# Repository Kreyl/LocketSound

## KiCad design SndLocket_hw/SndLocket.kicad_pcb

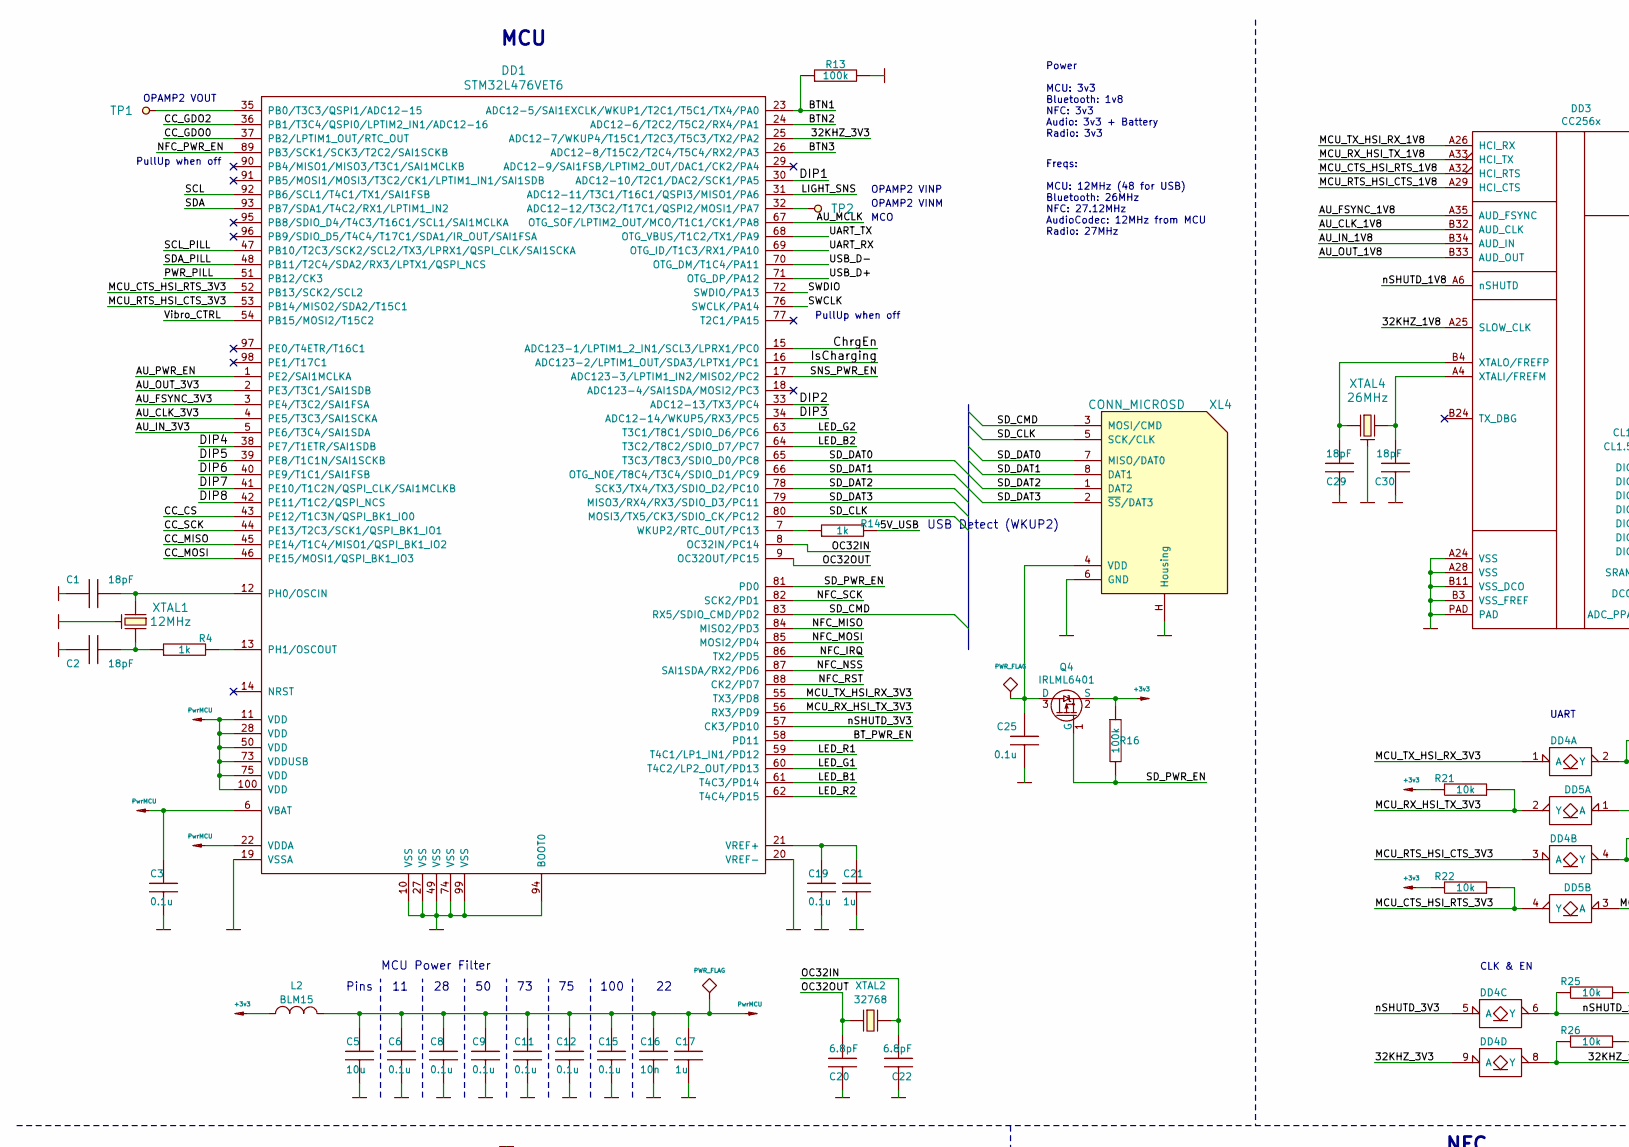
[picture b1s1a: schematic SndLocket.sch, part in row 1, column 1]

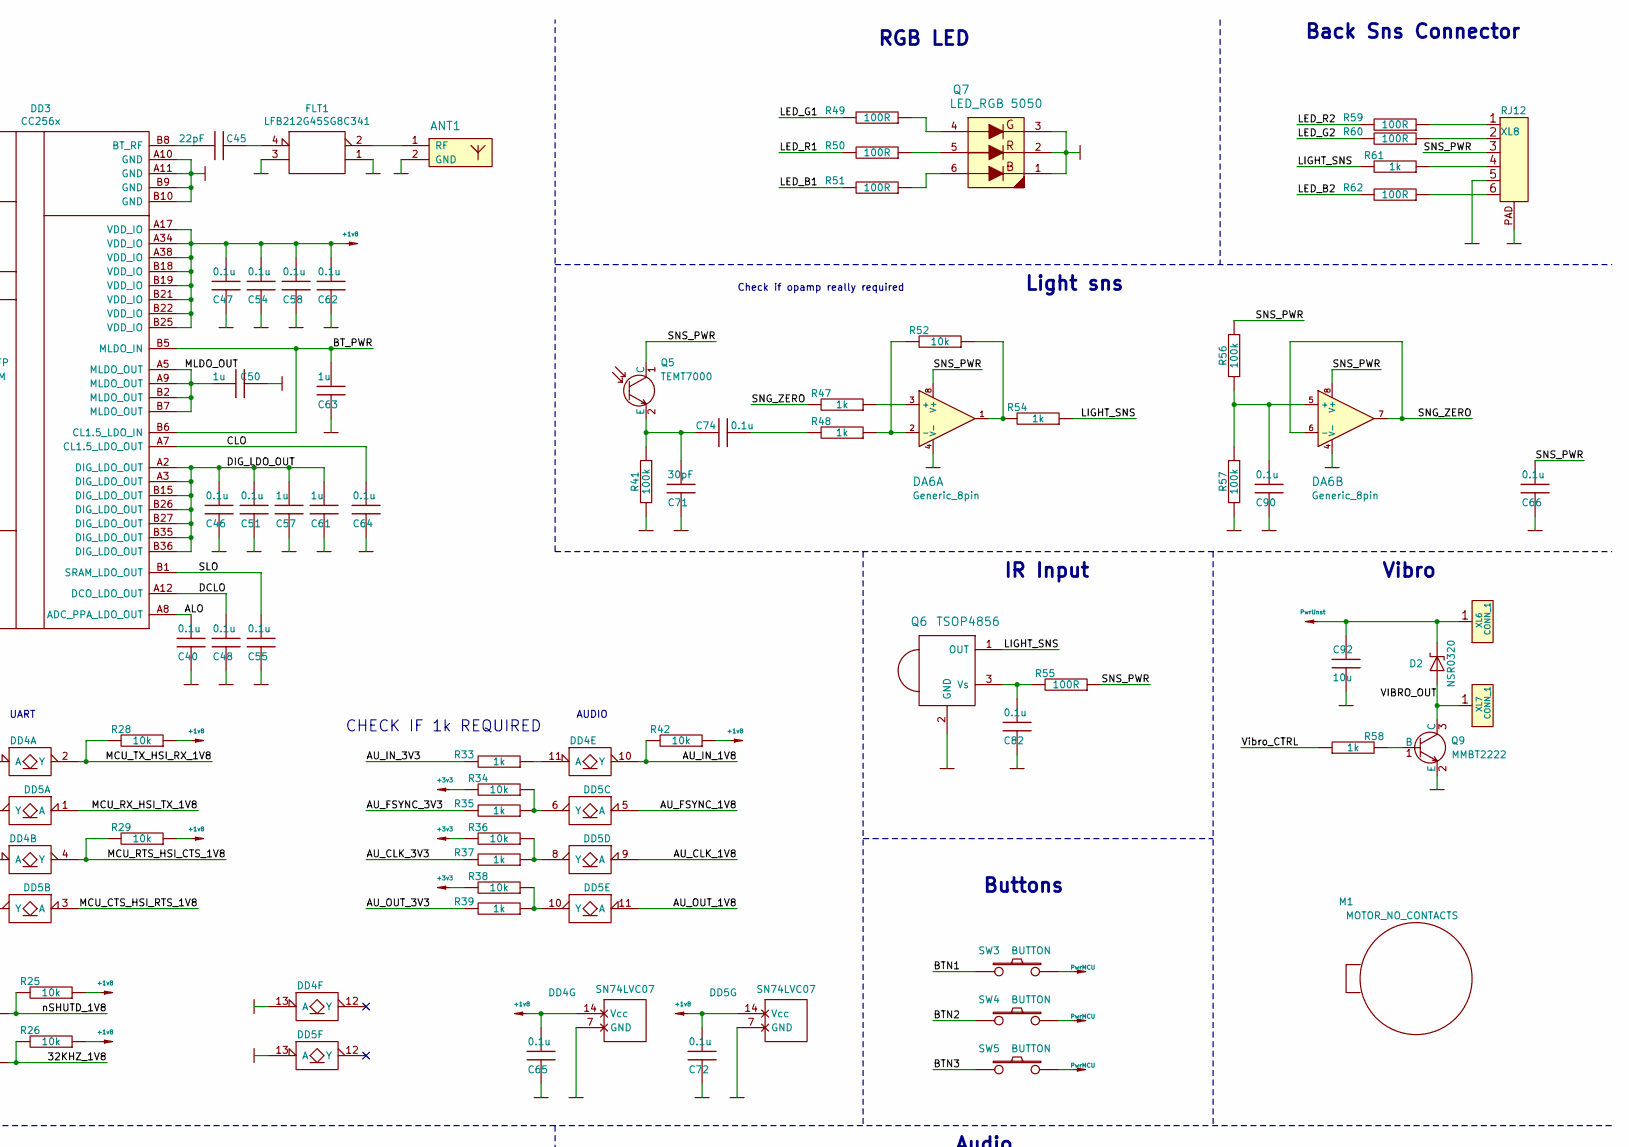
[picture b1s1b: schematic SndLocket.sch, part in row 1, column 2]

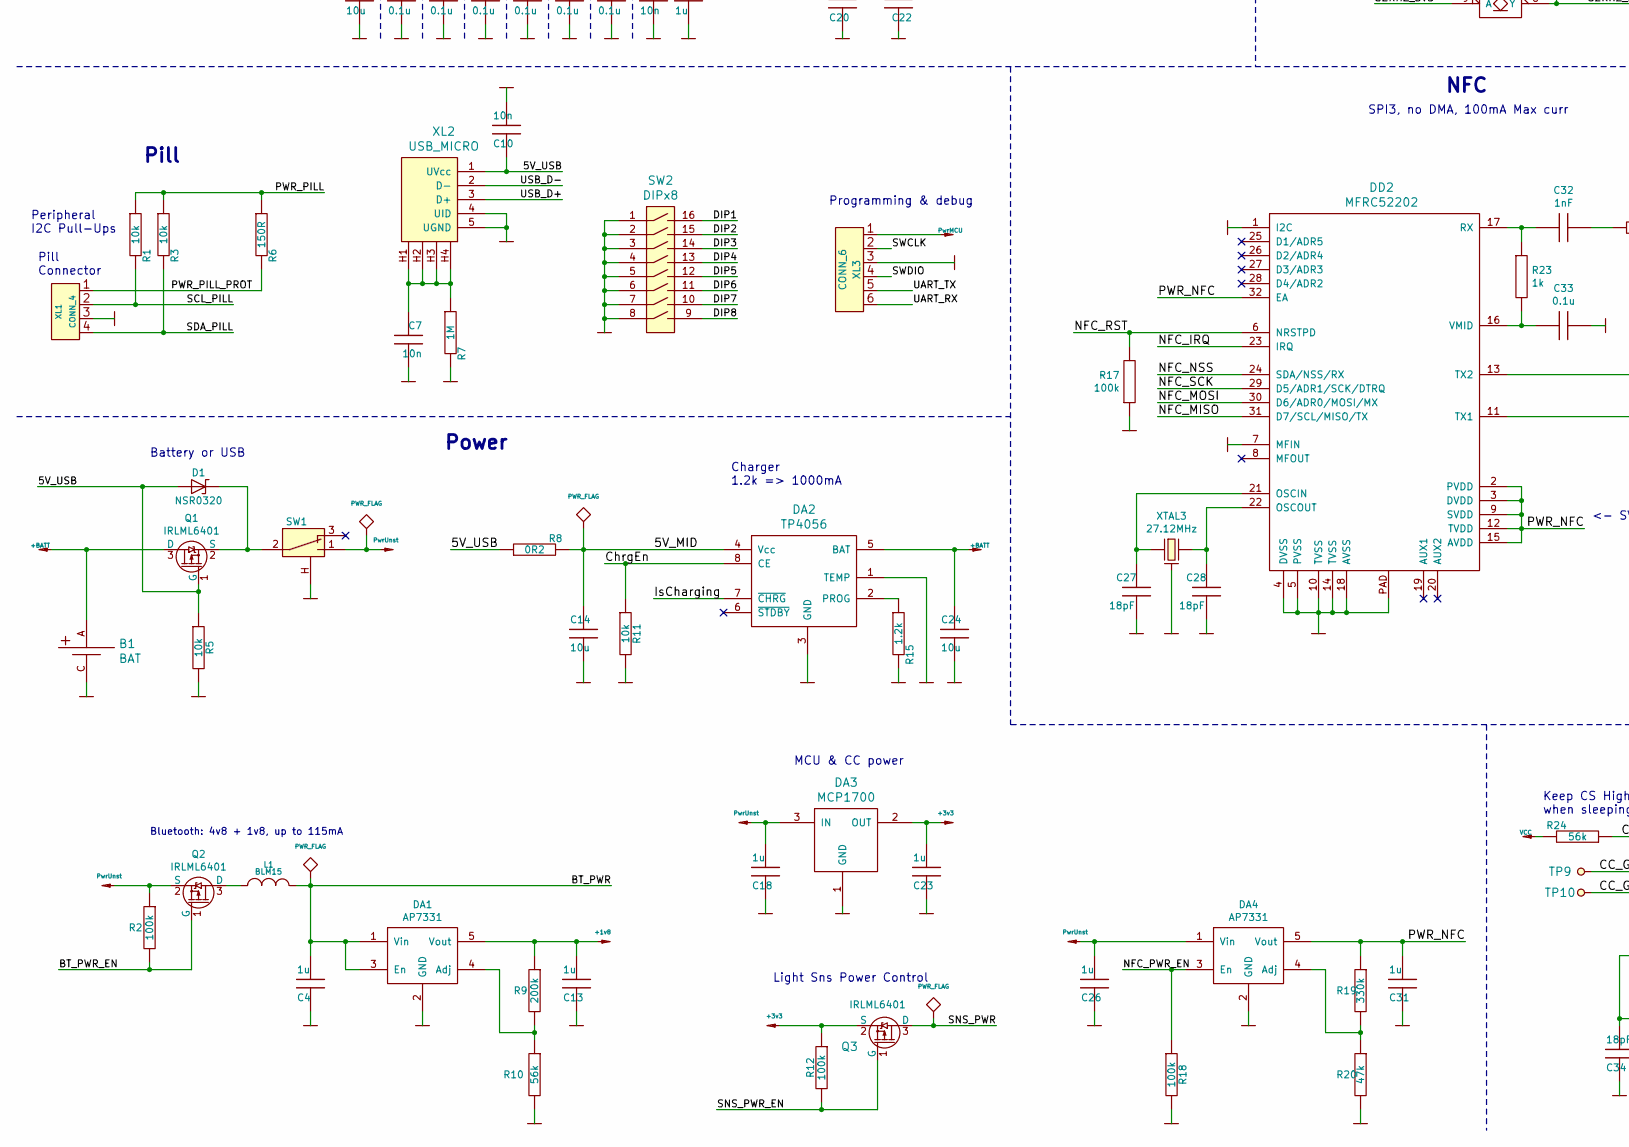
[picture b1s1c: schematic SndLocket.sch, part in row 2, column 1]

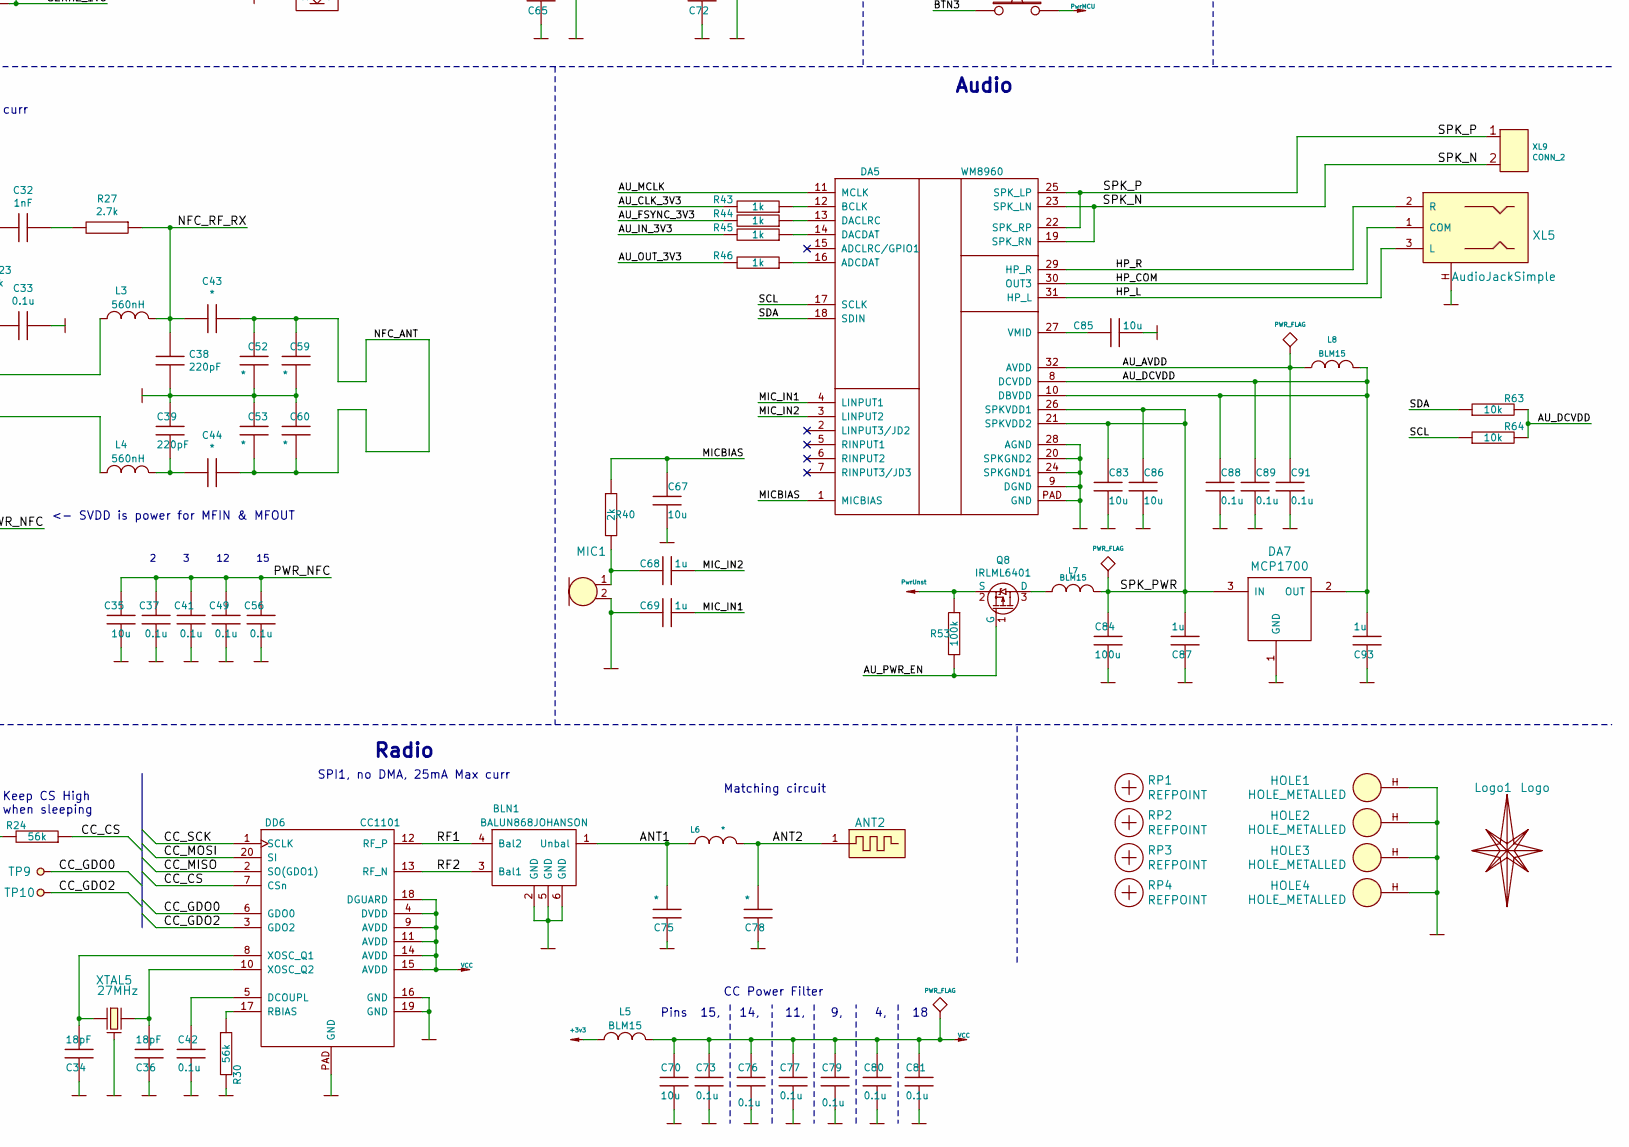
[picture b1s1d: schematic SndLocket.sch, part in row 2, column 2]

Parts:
ANT1: ANT_GENERAL; LcktSnd_2d41
ANT2: ANT_PCB_MONO_2PIN; LcktSnd_868
B1: BAT; 18650x1
BLN1: BALUN868JOHANSON; BALUN_JOHANSON868
C1, C2, C27, C28, C29, C30, C34, C36: 18pF; CAP_0603
C3, C6, C8, C9, C11, C12, C15, C19, C25, C33, C37, C40, C41, C42, C46, C47, C48, C49, C51, C54, C55, C56, C58, C62, C64, C65, C66, C72, C73, C74, C76, C77, C79, C80, C81, C82, C88, C89, C90, C91: 0.1u; CAP_0402
C4, C13, C17, C18, C21, C23, C26, C31, C50, C57, C61, C63, C68, C69, C87, C93: 1u; CAP_0603
C5, C14, C24, C35, C67, C70, C83, C85, C86, C92: 10u; CAP_0603
C7, C10, C16: 10n; CAP_0603
C20, C22: 6.8pF; CAP_0603
C32: 1nF; CAP_0603
C38, C39: 220pF; CAP_0603
C43, C44, C52, C53, C59, C60: *; CAP_0603
C45: 22pF; CAP_0402
C71: 30pF; CAP_0603
C75, C78: *; CAP_0402
C84: 100u; CAP_1206
D1, D2: NSR0320; SOD323
DA1, DA4: AP7331; SOT23-5
DA2: TP4056; SO8_150MIL
DA3, DA7: MCP1700; SOT23-3A
DA5: WM8960; QFN32_EP_5x5_Pitch0.5mm
DA6: Generic_8pin; SO8_150MIL
DD1: STM32L476VET6; LQFP100
DD2: MFRC52202; QFN32_EP_5x5_Pitch0.5mm
DD3: CC256x; mrQFN76
DD4, DD5: SN74LVC07; SO14
DD6: CC1101; QFN20
FLT1: LFB212G45SG8C341; FLT_LFB21
HOLE1, HOLE2, HOLE3, HOLE4: HOLE_METALLED; Hole2d2_out3d5mm
L1, L2, L5, L7, L8: BLM15; IND_0402
L3, L4: 560nH; IND_0805
L6: *; IND_0402
Logo1: Logo; Ostranna_12d7_10d1
M1: MOTOR_NO_CONTACTS; Motor_no_Contacts
MIC1: Microphone; PLS-2
Q1, Q2, Q3, Q4, Q8: IRLML6401; SOT23-3
Q5: TEMT7000; RES_1206
Q6: TSOP4856; TSOP48xx
Q7: LED_RGB 5050; LED_5050
Q9: MMBT2222; SOT23-3
R1, R3, R5, R11, R21, R22, R25, R26, R28, R29, R34, R36, R38, R42, R52, R63, R64: 10k; RES_0603
R2, R12, R13, R16, R17, R18, R41, R53, R56, R57: 100k; RES_0603
R4, R14, R23, R33, R35, R37, R39, R43, R44, R45, R46, R47, R48, R54, R58, R61: 1k; RES_0603
R6: 150R; RES_0603
R7: 1M; RES_0603
R8: 0R2; RES_1206
R9: 200k; RES_0603
R10, R24, R30: 56k; RES_0603
R15: 1.2k; RES_0603
R19: 330k; RES_0603
R20: 47k; RES_0603
R27: 2.7k; RES_0603
R40: 2k; RES_0603
R49, R50, R51, R55, R59, R60, R62: 100R; RES_0603
RP1, RP2, RP3, RP4: REFPOINT; REF_POINT_1MM
SW1: SWITCH; SW_SS-1P2T_Housing
SW2: DIPx8; DIP_SMD_X8
SW3, SW4, SW5: BUTTON; BTN_IT1198
TP1, TP2, TP9, TP10: TESTPOINT; TESTPOINT_1MM
XL1: CONN_4; PBS-4R
XL2: USB_MICRO; USBmicro_MOLEX_1050170001
XL3: CONN_6; PLS-6
XL4: CONN_MICROSD; MICROSD_EJECTOR_TFWF1
XL5: AudioJackSimple; AUDIO_CKX3_5_30
XL6, XL7: CONN_1; Oval3x1.5
XL8: RJ12; RJ11_TJ6_6P6C
XL9: CONN_2; SLD_2_2D5
XTAL1: 12MHz; 03225C4
XTAL2: 32768; 03215C2
XTAL3: 27.12MHz; 03225C4
XTAL4: 26MHz; 03225C4
XTAL5: 27MHz; 03225C4

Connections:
+1v8: C13.1, C47.1, C54.1, C58.1, C62.1, C65.1, C72.1, DA1.5 (Vout), DD3.A17 (VDD_IO), DD3.A34 (VDD_IO), DD3.A38 (VDD_IO), DD3.B18 (VDD_IO), DD3.B19 (VDD_IO), DD3.B21 (VDD_IO), DD3.B22 (VDD_IO), DD3.B25 (VDD_IO), DD4.14 (Vcc), DD5.14 (Vcc), R9.1, R25.1, R26.1, R28.1, R29.1, R42.1
+3v3: C23.1, DA3.2 (OUT), L2.2, L5.2, Q3.2 (S), Q4.2 (S), R12.1, R16.1, R21.2, R22.2, R34.2, R36.2, R38.2
+BATT: B1.A, C24.2, DA2.5 (BAT), Q1.3 (D)
/5V_MID: C14.2, DA2.4 (Vcc), R8.2
/5V_USB: C10.2, D1.A, Q1.1 (G), R5.1, R8.1, R14.2, XL2.1 (UVcc)
/32KHZ_1V8: DD3.A25 (SLOW_CLK), DD4.8 (Y), R26.2
/32KHZ_3V3: DD1.25 (ADC12-7/WKUP4/T15C1/T2C3/T5C3/TX2/PA2), DD4.9 (A)
/ALO: C40.1, DD3.A8 (ADC_PPA_LDO_OUT)
/ANT1: BLN1.1 (Unbal), C75.1, L6.2
/ANT2: ANT2.1, C78.1, L6.1
/AU_AVDD: C91.1, DA5.32 (AVDD), L8.1
/AU_CLK_1V8: DD3.B32 (AUD_CLK), DD5.9 (A)
/AU_CLK_3V3: DD1.4 (PE5/T3C3/SAI1SCKA), R37.2, R43.2
/AU_DCVDD: C88.1, C89.1, C93.1, DA5.8 (DCVDD), DA5.10 (DBVDD), DA7.2 (OUT), L8.2, R63.2, R64.2
/AU_FSYNC_1V8: DD3.A35 (AUD_FSYNC), DD5.5 (A)
/AU_FSYNC_3V3: DD1.3 (PE4/T3C2/SAI1FSA), R35.2, R44.2
/AU_IN_1V8: DD3.B34 (AUD_IN), DD4.10 (Y), R42.2
/AU_IN_3V3: DD1.5 (PE6/T3C4/SAI1SDA), R33.2, R45.2
/AU_MCLK: DA5.11 (MCLK), DD1.67 (OTG_SOF/LPTIM2_OUT/MCO/T1C1/CK1/PA8)
/AU_OUT_1V8: DD3.B33 (AUD_OUT), DD5.11 (A)
/AU_OUT_3V3: DD1.2 (PE3/T3C1/SAI1SDB), R39.2, R46.2
/AU_PWR_EN: DD1.1 (PE2/SAI1MCLKA), Q8.1 (G), R53.2
/BTN1: DD1.23 (ADC12-5/SAI1EXCLK/WKUP1/T2C1/T5C1/TX4/P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), R13.1, SW3.1
/BTN2: DD1.24 (ADC12-6/T2C2/T5C2/RX4/PA1), SW4.1
/BTN3: DD1.26 (ADC12-8/T15C2/T2C4/T5C4/RX2/PA3), SW5.1
/BT_PWR: C4.1, C63.1, DA1.1 (Vin), DA1.3 (En), DD3.B5 (MLDO_IN), DD3.B6 (CL1.5_LDO_IN), L1.1
/BT_PWR_EN: DD1.58 (PD11), Q2.1 (G), R2.2
/CC_CS: DD1.43 (PE12/T1C3N/QSPI_BK1_IO0), DD6.7 (CSn), R24.1
/CC_GDO0: DD1.37 (PB2/LPTIM1_OUT/RTC_OUT), DD6.6 (GDO0), TP9.1
/CC_GDO2: DD1.36 (PB1/T3C4/QSPI0/LPTIM2_IN1/ADC12-16), DD6.3 (GDO2), TP10.1
/CC_MISO: DD1.45 (PE14/T1C4/MISO1/QSPI_BK1_IO2), DD6.2 (SO(GDO1))
/CC_MOSI: DD1.46 (PE15/MOSI1/QSPI_BK1_IO3), DD6.20 (SI)
/CC_SCK: DD1.44 (PE13/T2C3/SCK1/QSPI_BK1_IO1), DD6.1 (SCLK)
/CLO: C64.1, DD3.A7 (CL1.5_LDO_OUT)
/ChrgEn: DA2.8 (CE), DD1.15 (ADC123-1/LPTIM1_2_IN1/SCL3/LPRX1/PC0), R11.1
/DCLO: C48.1, DD3.A12 (DCO_LDO_OUT)
/DIG_LDO_OUT: C46.1, C51.1, C57.1, C61.1, DD3.A2 (DIG_LDO_OUT), DD3.A3 (DIG_LDO_OUT), DD3.B15 (DIG_LDO_OUT), DD3.B26 (DIG_LDO_OUT), DD3.B27 (DIG_LDO_OUT), DD3.B35 (DIG_LDO_OUT), DD3.B36 (DIG_LDO_OUT)
/DIP1: DD1.30 (ADC12-10/T2C1/DAC2/SCK1/PA5), SW2.16
/DIP2: DD1.33 (ADC12-13/TX3/PC4), SW2.15
/DIP3: DD1.34 (ADC12-14/WKUP5/RX3/PC5), SW2.14
/DIP4: DD1.38 (PE7/T1ETR/SAI1SDB), SW2.13
/DIP5: DD1.39 (PE8/T1C1N/SAI1SCKB), SW2.12
/DIP6: DD1.40 (PE9/T1C1/SAI1FSB), SW2.11
/DIP7: DD1.41 (PE10/T1C2N/QSPI_CLK/SAI1MCLKB), SW2.10
/DIP8: DD1.42 (PE11/T1C2/QSPI_NCS), SW2.9
/HP_COM: DA5.30 (OUT3), XL5.1 (COM)
/HP_L: DA5.31 (HP_L), XL5.3 (L)
/HP_R: DA5.29 (HP_R), XL5.2 (R)
/IsCharging: DA2.7 (~CHRG), DD1.16 (ADC123-2/LPTIM1_OUT/SDA3/LPTX1/PC1)
/LED_B1: DD1.61 (T4C3/PD14), R51.2
/LED_B2: DD1.64 (T3C2/T8C2/SDIO_D7/PC7), R62.2
/LED_G1: DD1.60 (T4C2/LP2_OUT/PD13), R49.2
/LED_G2: DD1.63 (T3C1/T8C1/SDIO_D6/PC6), R60.2
/LED_R1: DD1.59 (T4C1/LP1_IN1/PD12), R50.2
/LED_R2: DD1.62 (T4C4/PD15), R59.2
/LIGHT_SNS: DD1.31 (ADC12-11/T3C1/T16C1/QSPI3/MISO1/PA6), Q6.1 (OUT), R54.1, R61.2
/MCU_CTS_HSI_RTS_1V8: DD3.A32 (HCI_RTS), DD5.3 (A)
/MCU_CTS_HSI_RTS_3V3: DD1.52 (PB13/SCK2/SCL2), DD5.4 (Y), R22.1
/MCU_RTS_HSI_CTS_1V8: DD3.A29 (HCI_CTS), DD4.4 (Y), R29.2
/MCU_RTS_HSI_CTS_3V3: DD1.53 (PB14/MISO2/SDA2/T15C1), DD4.3 (A)
/MCU_RX_HSI_TX_1V8: DD3.A33 (HCI_TX), DD5.1 (A)
/MCU_RX_HSI_TX_3V3: DD1.56 (RX3/PD9), DD5.2 (Y), R21.1
/MCU_TX_HSI_RX_1V8: DD3.A26 (HCI_RX), DD4.2 (Y), R28.2
/MCU_TX_HSI_RX_3V3: DD1.55 (TX3/PD8), DD4.1 (A)
/MICBIAS: C67.1, DA5.1 (MICBIAS), R40.1
/MIC_IN1: C69.1, DA5.4 (LINPUT1)
/MIC_IN2: C68.1, DA5.3 (LINPUT2)
/MLDO_OUT: C50.1, DD3.A5 (MLDO_OUT), DD3.A9 (MLDO_OUT), DD3.B2 (MLDO_OUT), DD3.B7 (MLDO_OUT)
/NFC_ANT: C43.1, C44.1, C52.1, C53.2, C59.1, C60.2
/NFC_IRQ: DD1.86 (TX2/PD5), DD2.23 (IRQ)
/NFC_MISO: DD1.84 (MISO2/PD3), DD2.31 (D7/SCL/MISO/TX)
/NFC_MOSI: DD1.85 (MOSI2/PD4), DD2.30 (D6/ADR0/MOSI/MX)
/NFC_NSS: DD1.87 (SAI1SDA/RX2/PD6), DD2.24 (SDA/NSS/RX)
/NFC_PWR_EN: DA4.3 (En), DD1.89 (PB3/SCK1/SCK3/T2C2/SAI1SCKB), R18.1
/NFC_RF_RX: C38.1, C43.2, L3.1, R27.1
/NFC_RST: DD1.88 (CK2/PD7), DD2.6 (NRSTPD), R17.2
/NFC_SCK: DD1.82 (SCK2/PD1), DD2.29 (D5/ADR1/SCK/DTRQ)
/OC32IN: C22.1, DD1.8 (OC32IN/PC14), XTAL2.2
/OC32OUT: C20.1, DD1.9 (OC32OUT/PC15), XTAL2.1
/PWR_NFC: C31.1, C35.2, C37.2, C41.2, C49.2, C56.2, DA4.5 (Vout), DD2.2 (PVDD), DD2.3 (DVDD), DD2.9 (SVDD), DD2.12 (TVDD), DD2.15 (AVDD), DD2.32 (EA), R19.1
/PWR_PILL: DD1.51 (PB12/CK3), R1.1, R3.1, R6.1
/PWR_PILL_PROT: R6.2, XL1.1
/RF1: BLN1.4 (Bal2), DD6.12 (RF_P)
/RF2: BLN1.3 (Bal1), DD6.13 (RF_N)
/SCL: DA5.17 (SCLK), DD1.92 (PB6/SCL1/T4C1/TX1/SAI1FSB), R64.1
/SCL_PILL: DD1.47 (PB10/T2C3/SCK2/SCL2/TX3/LPRX1/QSPI_CLK/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), R1.2, XL1.2 (PM)
/SDA: DA5.18 (SDIN), DD1.93 (PB7/SDA1/T4C2/RX1/LPTIM1_IN2), R63.1
/SDA_PILL: DD1.48 (PB11/T2C4/SDA2/RX3/LPTX1/QSPI_NCS), R3.2, XL1.4
/SD_CLK: DD1.80 (MOSI3/TX5/CK3/SDIO_CK/PC12), XL4.5 (SCK/CLK)
/SD_CMD: DD1.83 (RX5/SDIO_CMD/PD2), XL4.3 (MOSI/CMD)
/SD_DAT0: DD1.65 (T3C3/T8C3/SDIO_D0/PC8), XL4.7 (MISO/DAT0)
/SD_DAT1: DD1.66 (OTG_NOE/T8C4/T3C4/SDIO_D1/PC9), XL4.8 (DAT1)
/SD_DAT2: DD1.78 (SCK3/TX4/TX3/SDIO_D2/PC10), XL4.1 (DAT2)
/SD_DAT3: DD1.79 (MISO3/RX4/RX3/SDIO_D3/PC11), XL4.2 (~SS~/DAT3)
/SD_PWR_EN: DD1.81 (PD0), Q4.1 (G), R16.2
/SLO: C55.1, DD3.B1 (SRAM_LDO_OUT)
/SNG_ZERO: DA6.6 (-), DA6.7, R47.2
/SNS_PWR: C66.1, DA6.8 (V+), Q3.3 (D), Q5.1 (C), R55.1, R56.1, XL8.3
/SNS_PWR_EN: DD1.17 (ADC123-3/LPTIM1_IN2/MISO2/PC2), Q3.1 (G), R12.2
/SPK_N: DA5.19 (SPK_RN), DA5.23 (SPK_LN), XL9.2 (PM)
/SPK_P: DA5.22 (SPK_RP), DA5.25 (SPK_LP), XL9.1
/SPK_PWR: C83.1, C84.1, C86.1, C87.1, DA5.21 (SPKVDD2), DA5.26 (SPKVDD1), DA7.3 (IN), L7.1
/SWCLK: DD1.76 (SWCLK/PA14), XL3.2
/SWDIO: DD1.72 (SWDIO/PA13), XL3.4
/UART_RX: DD1.69 (OTG_ID/T1C3/RX1/PA10), XL3.6
/UART_TX: DD1.68 (OTG_VBUS/T1C2/TX1/PA9), XL3.5
/USB_D+: DD1.71 (OTG_DP/PA12), XL2.3 (D+)
/USB_D-: DD1.70 (OTG_DM/T1C4/PA11), XL2.2 (D-)
/VIBRO_OUT: D2.A, Q9.3 (C), XL7.1
/Vibro_CTRL: DD1.54 (PB15/MOSI2/T15C2), R58.1
/nSHUTD_1V8: DD3.A6 (nSHUTD), DD4.6 (Y), R25.2
/nSHUTD_3V3: DD1.57 (CK3/PD10), DD4.5 (A)
GND: ANT1.2 (GND), B1.C, BLN1.2 (GND), BLN1.5 (GND), BLN1.6 (GND), C1.2, C2.2, C3.1, C4.2, C5.1, C6.1, C7.1, C8.1, C9.1, C10.1, C11.1, C12.1, C13.2, C14.1, C15.1, C16.1, C17.1, C18.2, C19.1, C20.2, C21.1, C22.2, C23.2, C24.1, C25.2, C26.2, C27.2, C28.2, C29.2, C30.2, C31.2, C33.1, C34.2, C35.1, C36.2, C37.1, C38.2, C39.1, C40.2, C41.1, C42.1, C46.2, C47.2, C48.2, C49.1, C50.2, C51.2, C52.2, C53.1, C54.2, C55.2, C56.1, C57.2, C58.2, C59.2, C60.1, C61.2, C62.2, C63.2, C64.2, C65.2, C66.2, C67.2, C69.2, C70.2, C71.2, C72.2, C73.2, C75.2, C76.2, C77.2, C78.2, C79.2, C80.2, C81.2, C82.2, C83.2, C84.2, C85.2, C86.2, C87.2, C88.2, C89.2, C90.2, C91.2, C92.1, C93.2, DA1.2 (GND), DA2.1 (TEMP), DA2.3 (GND), DA3.1 (GND), DA4.2 (GND), DA5.9 (DGND), DA5.20 (SPKGND2), DA5.24 (SPKGND1), DA5.28 (AGND), DA5.PAD (GND), DA6.4 (V-), DA7.1 (GND), DD1.10 (VSS), DD1.19 (VSSA), DD1.20 (VREF-), DD1.27 (VSS), DD1.49 (VSS), DD1.74 (VSS), DD1.94 (BOOT0), DD1.99 (VSS), DD2.1 (I2C), DD2.4 (DVSS), DD2.5 (PVSS), DD2.7 (MFIN), DD2.10 (TVSS), DD2.14 (TVSS), DD2.18 (AVSS), DD2.PAD, DD3.A10 (GND), DD3.A11 (GND), DD3.A24 (VSS), DD3.A28 (VSS), DD3.B3 (VSS_FREF), DD3.B9 (GND), DD3.B10 (GND), DD3.B11 (VSS_DCO), DD3.PAD, DD4.7 (GND), DD4.13 (A), DD5.7 (GND), DD5.13 (A), DD6.16 (GND), DD6.19 (GND), DD6.PAD (GND), FLT1.1, FLT1.3, HOLE1.H, HOLE2.H, HOLE3.H, HOLE4.H, MIC1.2, Q6.2 (GND), Q7.1, Q7.2, Q7.3, Q9.2 (E), R5.2, R7.2, R10.2, R11.2, R13.2, R15.2, R17.1, R18.2, R20.2, R30.2, R41.2, R57.2, SW1.H, SW2.1, SW2.2, SW2.3, SW2.4, SW2.5, SW2.6, SW2.7, SW2.8, XL1.3, XL2.4 (UID), XL2.5 (UGND), XL3.3, XL4.6 (GND), XL4.H (Housing), XL5.H, XL8.5, XL8.PAD, XTAL1.H, XTAL3.H, XTAL4.H, XTAL5.H
unnamed: ANT1.1 (RF), FLT1.2
unnamed: C1.1, DD1.12 (PH0/OSCIN), XTAL1.1
unnamed: C2.1, R4.1, XTAL1.2
unnamed: C7.2, R7.1, XL2.H1, XL2.H2, XL2.H3, XL2.H4
unnamed: C19.2, C21.2, DD1.21 (VREF+)
unnamed: C25.1, Q4.3 (D), XL4.4 (VDD)
unnamed: C27.1, DD2.21 (OSCIN), XTAL3.1
unnamed: C28.1, DD2.22 (OSCOUT), XTAL3.2
unnamed: C29.1, DD3.B4 (XTALO/FREFP), XTAL4.1
unnamed: C30.1, DD3.A4 (XTALI/FREFM), XTAL4.2
unnamed: C32.1, R27.2
unnamed: C32.2, DD2.17 (RX), R23.1
unnamed: C33.2, DD2.16 (VMID), R23.2
unnamed: C34.1, DD6.8 (XOSC_Q1), XTAL5.1
unnamed: C36.1, DD6.10 (XOSC_Q2), XTAL5.2
unnamed: C39.2, C44.2, L4.1
unnamed: C42.2, DD6.5 (DCOUPL)
unnamed: C45.1, DD3.B8 (BT_RF)
unnamed: C45.2, FLT1.4
unnamed: C68.2, MIC1.1, R40.2
unnamed: C71.1, C74.2, Q5.2 (E), R41.1
unnamed: C74.1, R48.2
unnamed: C82.1, Q6.3 (Vs), R55.2
unnamed: C85.1, DA5.27 (VMID)
unnamed: C90.1, DA6.5 (+), R56.2, R57.1
unnamed: D1.C, Q1.2 (S), SW1.2
unnamed: DA1.4 (Adj), R9.2, R10.1
unnamed: DA2.2 (PROG), R15.1
unnamed: DA4.4 (Adj), R19.2, R20.1
unnamed: DA5.12 (BCLK), R43.1
unnamed: DA5.13 (DACLRC), R44.1
unnamed: DA5.14 (DACDAT), R45.1
unnamed: DA5.16 (ADCDAT), R46.1
unnamed: DA6.1, R52.1, R54.2
unnamed: DA6.2 (-), R48.1, R52.2
unnamed: DA6.3 (+), R47.1
unnamed: DD1.7 (WKUP2/RTC_OUT/PC13), R14.1
unnamed: DD1.13 (PH1/OSCOUT), R4.2
unnamed: DD1.32 (ADC12-12/T3C2/T17C1/QSPI2/MOSI1/PA7), TP2.1
unnamed: DD1.35 (PB0/T3C3/QSPI1/ADC12-15), TP1.1
unnamed: DD2.11 (TX1), L4.2
unnamed: DD2.13 (TX2), L3.2
unnamed: DD4.11 (A), R33.1
unnamed: DD5.6 (Y), R34.1, R35.1
unnamed: DD5.8 (Y), R36.1, R37.1
unnamed: DD5.10 (Y), R38.1, R39.1
unnamed: DD6.17 (RBIAS), R30.1
unnamed: L1.2, Q2.3 (D)
unnamed: L7.2, Q8.3 (D)
unnamed: Q7.4 (B), R49.1
unnamed: Q7.5 (G), R50.1
unnamed: Q7.6, R51.1
unnamed: Q9.1 (B), R58.2
unnamed: R59.1, XL8.1
unnamed: R60.1, XL8.2
unnamed: R61.1, XL8.4
unnamed: R62.1, XL8.6
PwrMCU: C3.2, C5.2, C6.2, C8.2, C9.2, C11.2, C12.2, C15.2, C16.2, C17.2, DD1.6 (VBAT), DD1.11 (VDD), DD1.22 (VDDA), DD1.28 (VDD), DD1.50 (VDD), DD1.73 (VDDUSB), DD1.75 (VDD), DD1.100 (VDD), L2.1, SW3.2, SW4.2, SW5.2, XL3.1
PwrUnst: C18.1, C26.1, C92.2, D2.C, DA3.3 (IN), DA4.1 (Vin), Q2.2 (S), Q8.2 (S), R2.1, R53.1, SW1.1, XL6.1
VCC: C70.1, C73.1, C76.1, C77.1, C79.1, C80.1, C81.1, DD6.4 (DVDD), DD6.9 (AVDD), DD6.11 (AVDD), DD6.14 (AVDD), DD6.15 (AVDD), DD6.18 (DGUARD), L5.1, R24.2

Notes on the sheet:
Audio
MCU & CC power
Power
Charger 1.2k => 1000mA
Battery or USB
IR Input
Vibro
MCU
RGB LED
Back Sns Connector
Light sns
Light Sns Power Control
Programming & debug
Peripheral I2C Pull-Ups
Pill Connector
Pill
Buttons
2 3 12 15
NFC
SPI3, no DMA, 100mA Max curr
<- SVDD is power for MFIN & MFOUT
Radio
Matching circuit
Keep CS High when sleeping
SPI1, no DMA, 25mA Max curr
CC Power Filter
Pins 15, 14, 11, 9, 4, 18
MCO
MCU Power Filter
Pins 11 28 50 73 75 100 22
USB Detect (WKUP2)
OPAMP2 VINP
OPAMP2 VINM
OPAMP2 VOUT
Check if opamp really required
UART
AUDIO
CLK & EN
CHECK IF 1k REQUIRED
Freqs: MCU: 12MHz (48 for USB) Bluetooth: 26MHz NFC: 27.12MHz AudioCodec: 12MHz from MCU Radio: 27MHz

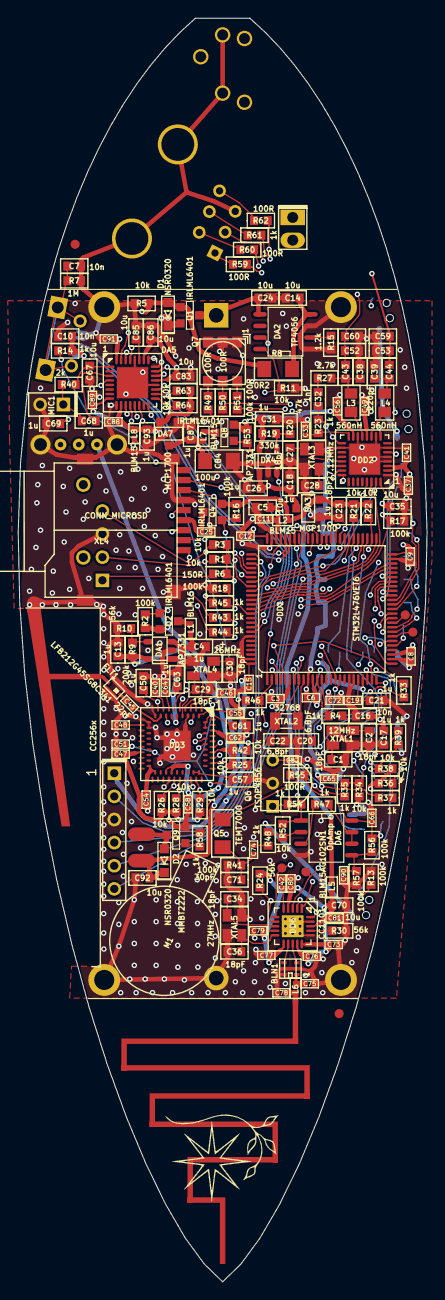
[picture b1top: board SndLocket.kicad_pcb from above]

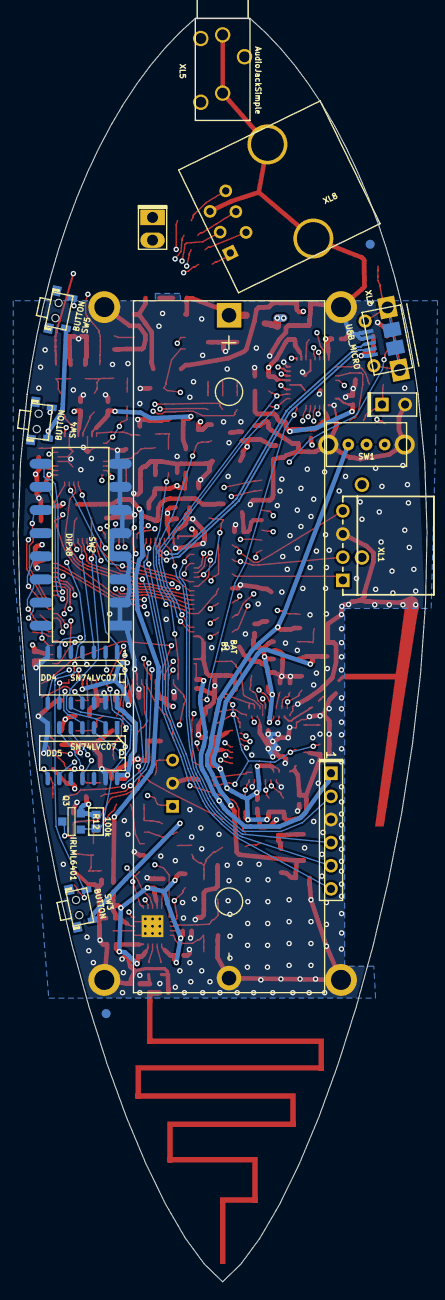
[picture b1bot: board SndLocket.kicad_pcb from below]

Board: 4 copper layers, 44.9 x 138.8 mm, 226 parts (17 on the bottom side), 173 nets.

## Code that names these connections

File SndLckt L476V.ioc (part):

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Mcu.Name=STM32L476V(C-E-G)Tx
Mcu.Package=LQFP100
Mcu.UserName=STM32L476VGTx
PA0.Mode=SYS_WakeUp0
PA0.Signal=SYS_WKUP1
PA1.Signal=GPIO_Input
PA10.Mode=Asynchronous
PA10.Signal=USART1_RX
PA11.Mode=Device_Only
PA11.Signal=USB_OTG_FS_DM
PA12.Mode=Device_Only
PA12.Signal=USB_OTG_FS_DP
PA13\ (JTMS-SWDIO).Mode=Serial_Wire
PA13\ (JTMS-SWDIO).Signal=SYS_JTMS-SWDIO
PA14\ (JTCK-SWCLK).Mode=Serial_Wire
PA14\ (JTCK-SWCLK).Signal=SYS_JTCK-SWCLK
PA2.Mode=Clock-out-LSCO
PA2.Signal=RCC_LSCO
PA3.Signal=GPIO_Input
PA6.Mode=Standalone
PA6.Signal=OPAMP2_VINP
PA7.Mode=Standalone
PA7.Signal=OPAMP2_VINM
PA8.Mode=Clock-out
PA8.Signal=RCC_MCO
PA9.Mode=Asynchronous
PA9.Signal=USART1_TX
PB0.Mode=Standalone
PB0.Signal=OPAMP2_VOUT
PB1.Signal=GPIO_Input
PB10.Mode=I2C
PB10.Signal=I2C2_SCL
PB11.Mode=I2C
PB11.Signal=I2C2_SDA
PB12.Signal=GPIO_Output
PB13.Mode=CTS_RTS
PB13.Signal=USART3_CTS
PB14.Mode=CTS_RTS
PB14.Signal=USART3_RTS
PB15.Signal=S_TIM15_CH2
PB2.Signal=GPIO_Input
PB3\ (JTDO-TRACESWO).Signal=GPIO_Output
PB6.Mode=I2C
PB6.Signal=I2C1_SCL
PB7.Mode=I2C
PB7.Signal=I2C1_SDA
PC0.Signal=GPIO_Input
PC1.Signal=GPIO_Output
PC10.Mode=SD_4_bits_Wide_bus
PC10.Signal=SDMMC1_D2
PC11.Mode=SD_4_bits_Wide_bus
PC11.Signal=SDMMC1_D3
PC12.Mode=SD_4_bits_Wide_bus
PC12.Signal=SDMMC1_CK
PC13.Mode=SYS_WakeUp1
PC13.Signal=SYS_WKUP2
PC14-OSC32_IN\ (PC14).Mode=LSE-External-Oscillator
PC14-OSC32_IN\ (PC14).Signal=RCC_OSC32_IN
PC15-OSC32_OUT\ (PC15).Mode=LSE-External-Oscillator
PC15-OSC32_OUT\ (PC15).Signal=RCC_OSC32_OUT
PC2.Signal=GPIO_Output
PC6.Signal=S_TIM3_CH1
PC7.Signal=S_TIM3_CH2
PC8.Mode=SD_4_bits_Wide_bus
PC8.Signal=SDMMC1_D0
PC9.Mode=SD_4_bits_Wide_bus
PC9.Signal=SDMMC1_D1
PD0.Signal=GPIO_Output
PD1.Mode=Full_Duplex_Master
PD1.Signal=SPI2_SCK
PD10.Signal=GPIO_Output
PD11.Signal=GPIO_Output
PD12.Signal=S_TIM4_CH1
PD13.Signal=S_TIM4_CH2
PD14.Signal=S_TIM4_CH3
PD15.Signal=S_TIM4_CH4
PD2.Mode=SD_4_bits_Wide_bus
PD2.Signal=SDMMC1_CMD
PD3.Mode=Full_Duplex_Master
PD3.Signal=SPI2_MISO
PD4.Mode=Full_Duplex_Master
PD4.Signal=SPI2_MOSI
PD5.Signal=GPIO_Input
PD6.Signal=GPIO_Output
PD7.Signal=GPIO_Output
PD8.Mode=Asynchronous
PD8.Signal=USART3_TX
PD9.Mode=Asynchronous
PD9.Signal=USART3_RX
PE12.Signal=GPIO_Output
PE13.Mode=Full_Duplex_Master
PE13.Signal=SPI1_SCK
PE14.Mode=Full_Duplex_Master
PE14.Signal=SPI1_MISO
PE15.Mode=Full_Duplex_Master
PE15.Signal=SPI1_MOSI
PE2.Signal=GPIO_Output
PE3.Mode=SAI_B_SyncSlave
PE3.Signal=SAI1_SD_B
PE4.Mode=SAI_A_AsyncSlave
PE4.Signal=SAI1_FS_A
PE5.Mode=SAI_A_AsyncSlave
PE5.Signal=SAI1_SCK_A
PE6.Mode=SAI_A_AsyncSlave
PE6.Signal=SAI1_SD_A
PH0-OSC_IN\ (PH0).Mode=HSE-External-Oscillator
PH0-OSC_IN\ (PH0).Signal=RCC_OSC_IN
PH1-OSC_OUT\ (PH1).Mode=HSE-External-Oscillator
PH1-OSC_OUT\ (PH1).Signal=RCC_OSC_OUT
RCC.HSE_VALUE=12000000
RCC.SYSCLKFreq_VALUE=80000000
RCC.SYSCLKSource=RCC_SYSCLKSOURCE_PLLCLK
board=custom

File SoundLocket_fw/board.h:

#pragma once

// ==== General ====
#define APP_NAME            "SndLckt1"

// Version of PCB
#define PCB_VER                 1

// MCU type as defined in the ST header.
#define STM32L476xx

// Freq of external crystal if any. Leave it here even if not used.
#define CRYSTAL_FREQ_HZ         12000000

// OS timer settings
#define STM32_ST_IRQ_PRIORITY   2
#define STM32_ST_USE_TIMER      5
#define SYS_TIM_CLK             (Clk.APB1FreqHz)    // Timer 5 is clocked by APB1

//  Periphery
#define I2C1_ENABLED            FALSE
#define I2C2_ENABLED            FALSE
#define I2C3_ENABLED            FALSE
#define SIMPLESENSORS_ENABLED   FALSE
#define BUTTONS_ENABLED         FALSE

#define ADC_REQUIRED            FALSE
#define STM32_DMA_REQUIRED      TRUE    // Leave this macro name for OS

#if 1 // ========================== GPIO =======================================
// EXTI
#define INDIVIDUAL_EXTI_IRQ_REQUIRED    FALSE

// Buttons
#define BTN1_PIN        GPIOA, 0
#define BTN2_PIN        GPIOA, 1
#define BTN3_PIN        GPIOA, 3

// Vibro
#define VIBRO_CTRL      { GPIOB, 15, TIM15, 2, invNotInverted, omPushPull, 99 }

// Battery
#define IS_CHARGING     GPIOC, 1, pudPullUp
#define BAT_MEAS_EN     GPIOA, 5
#define BAT_ADC_PIN     GPIOB, 1

// Light
#define LED_R1_PIN      { GPIOD, 12, TIM4, 1, invNotInverted, omPushPull, 255 }
#define LED_G1_PIN      { GPIOD, 13, TIM4, 2, invNotInverted, omPushPull, 255 }
#define LED_B1_PIN      { GPIOD, 14, TIM4, 3, invNotInverted, omPushPull, 255 }
#define LED_R2_PIN      { GPIOD, 15, TIM4, 4, invNotInverted, omPushPull, 255 }
#define LED_G2_PIN      { GPIOC,  6, TIM3, 1, invNotInverted, omPushPull, 255 }
#define LED_B2_PIN      { GPIOC,  7, TIM3, 2, invNotInverted, omPushPull, 255 }

// USB
#define USB_DM          GPIOA, 11
#define USB_DP          GPIOA, 12
#define USB_AF          AF10
#define USB_DETECT_PIN  GPIOA, 7

// Radio: SPI, PGpio, Sck, Miso, Mosi, Cs, Gdo0
#define CC_Setup0       SPI1, GPIOB, 3,4,5, GPIOA,15, GPIOB,0

// UART
#define UART_GPIO       GPIOA
#define UART_TX_PIN     9
#define UART_RX_PIN     10

// I2C
#define I2C1_GPIO       GPIOB
#define I2C1_SCL        8
#define I2C1_SDA        9
// I2C Alternate Function
#define I2C_AF          AF4

// Sensor
#define SNS_PWR_EN      GPIOC, 2

#define EE_PWR_PIN      GPIOB, 10

#endif // GPIO

#if 1 // =========================== I2C =======================================
// i2cclkPCLK1, i2cclkSYSCLK, i2cclkHSI
#define I2C_CLK_SRC     i2cclkHSI
#define I2C_BAUDRATE_HZ 400000
#endif

#if ADC_REQUIRED // ======================= Inner ADC ==========================
// Clock divider: clock is generated from the APB2
#define ADC_CLK_DIVIDER		adcDiv2

// ADC channels
#define ADC_BATTERY_CHNL 	14
// ADC_VREFINT_CHNL
#define ADC_CHANNELS        { ADC_BATTERY_CHNL, ADC_VREFINT_CHNL }
#define ADC_CHANNEL_CNT     2   // Do not use countof(AdcChannels) as preprocessor does not know what is countof => cannot check
#define ADC_SAMPLE_TIME     ast24d5Cycles
#define ADC_OVERSAMPLING_RATIO  64   // 1 (no oversampling), 2, 4, 8, 16, 32, 64, 128, 256
#endif

#if 1 // =========================== DMA =======================================
// ==== Uart ====
// Remap is made automatically if required
#define UART_DMA_TX     STM32_DMA_STREAM_ID(2, 6)
#define UART_DMA_RX     STM32_DMA_STREAM_ID(2, 7)
#define UART_DMA_CHNL   2
#define UART_DMA_TX_MODE(Chnl) (STM32_DMA_CR_CHSEL(Chnl) | DMA_PRIORITY_LOW | STM32_DMA_CR_MSIZE_BYTE | STM32_DMA_CR_PSIZE_BYTE | STM32_DMA_CR_MINC | STM32_DMA_CR_DIR_M2P | STM32_DMA_CR_TCIE)
#define UART_DMA_RX_MODE(Chnl) (STM32_DMA_CR_CHSEL(Chnl) | DMA_PRIORITY_MEDIUM | STM32_DMA_CR_MSIZE_BYTE | STM32_DMA_CR_PSIZE_BYTE | STM32_DMA_CR_MINC | STM32_DMA_CR_DIR_P2M | STM32_DMA_CR_CIRC)

// ==== ACG ====
#define ACG_DMA_TX      STM32_DMA_STREAM_ID(1, 5)
#define ACG_DMA_RX      STM32_DMA_STREAM_ID(1, 4)
#define ACG_DMA_CHNL    1

// ==== I2C ====
#define I2C1_DMA_TX     STM32_DMA_STREAM_ID(1, 6)
#define I2C1_DMA_RX     STM32_DMA_STREAM_ID(1, 7)
#define I2C1_DMA_CHNL   3

#if ADC_REQUIRED
#define ADC_DMA         STM32_DMA1_STREAM1
#define ADC_DMA_MODE    STM32_DMA_CR_CHSEL(0) |   /* DMA1 Stream1 Channel0 */ \
                        DMA_PRIORITY_LOW | \
                        STM32_DMA_CR_MSIZE_HWORD | \
                        STM32_DMA_CR_PSIZE_HWORD | \
                        STM32_DMA_CR_MINC |       /* Memory pointer increase */ \
                        STM32_DMA_CR_DIR_P2M |    /* Direction is peripheral to memory */ \
                        STM32_DMA_CR_TCIE         /* Enable Transmission Complete IRQ */
#endif // ADC

#endif // DMA

#if 1 // ========================== USART ======================================
#define PRINTF_FLOAT_EN FALSE
#define UART_TXBUF_SZ   8192
#define UART_RXBUF_SZ   99

#define UARTS_CNT       1

#define CMD_UART_PARAMS \
    USART1, UART_GPIO, UART_TX_PIN, UART_GPIO, UART_RX_PIN, \
    UART_DMA_TX, UART_DMA_RX, UART_DMA_TX_MODE(UART_DMA_CHNL), UART_DMA_RX_MODE(UART_DMA_CHNL), \
    true // Use independent clock

#endif

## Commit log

2019-02-04 Proceeding w sch
2019-02-06 Proceeding
2019-02-08 Sound routing done
2019-02-12 no message
2019-02-13 + pcb shape
2019-02-23 Sent to factory
2019-03-19 minor
2019-03-19 Proceeding w os adaptation
2019-03-20 First answer of firmware
2019-04-01 IR RX in progress
2022-02-10 Something
